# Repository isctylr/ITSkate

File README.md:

# ITSkate
The collection of hardware and software for my electric skateboard project.

The only portion currently available is the remote, which can be found in the "Remote" folder.
  - This includes the hardware for the remote (TX), joystick, and receiver (RX), plus software. More information available in the folder.

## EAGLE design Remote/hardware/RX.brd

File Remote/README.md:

# ITSkate Remote

An open source remote for the VESC based on the arduino samd architecture and the HM-10 BLE module.

To build the board from scratch will require the following items:
	- All 3 finished boards (A BOM is in the works, but can be determined from the EAGLE files under "Hardware").
	- The Arduino IDE with the Arduino SAMD boards installed.
	- The bootloader, which can be loaded by adding http://isaactaylor.net/package_itaylor_index.json to Preferences>Additional Boards Manager URLs, and installing ITSkate Remote from the Board Manager.
	- A j-link, stlink v2, or other programmer for the samd chip. (This guide will use the stlink v2).

## Building the board

## Programming the HM-10s

Programming the HM-10 module takes 6 steps, using the AT commands. You may choose to perform this step later, as the TX software includes an AT passthrough mode.

You can learn more about the HM-10 and it's AT commands from the manual: http://fab.cba.mit.edu/classes/863.15/doc/tutorials/programming/bluetooth/bluetooth40_en.pdf

1. AT
You should recieve OK in return. If nothing appears, make sure you have a genuine HM10 and not a clone, then make sure you are not sending LF or CR, and that your baud rate is 9600 (we will be changing this later, but this is the default).

2. AT+ADDR?
Take note of the address of both the RX and TX.

3. AT+ROLE?
Setting the role will depend on if this is the TX or RX. The TX will be set to AT+ROLE1, because it is the master device. The RX will be set to AT+ROLE0 (left as default).

4. AT+CONxxxxxxxx
Replace the xxxxx with the address of the opposite board, performing the command first on the RX board, then the TX. If both are powered on, you should recieve OK+CONN from the TX.

5. AT+POWE3
Boost the power on both to 6dbm.

6. AT+BAUD4
Set the baud rate of the UART connection to 115200. 

7. AT+RESET
After resetting you'll have to reconnect with the baud rate of 115200. You can type AT to check your work.

## Building the bootloader

## Flashing the bootloader

## Loading the software

Download VescUartControl library by RollingGecko Make sure to choose the
VESC6 branch if you program your vesc with vesc-tool and not bldc.
Add the following lines to VescUart.h:

#ifdef ARDUINO_ARCH_SAMD
#define SERIALIO Serial1  
#define DEBUGSERIAL Serial
#endif

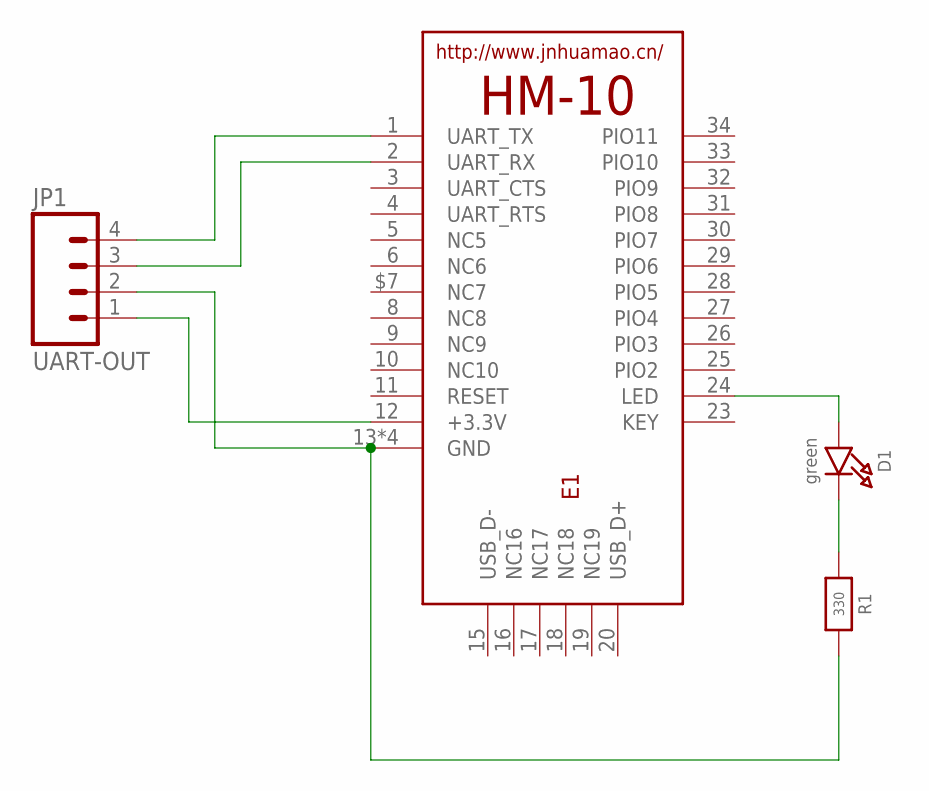
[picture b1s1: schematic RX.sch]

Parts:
D1: green; CHIPLED_0805_NOOUTLINE
E1: HM-10-BOARD; 26.9X13X2.2_BOARD
JP1: UART-OUT; 1X04
R1: 330; 0805-NO

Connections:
unnamed: E1.1 (UART_TX), JP1.4
unnamed: E1.2 (UART_RX), JP1.3
unnamed: E1.13 (GND), E1.14 (GND), E1.21 (GND), E1.22 (GND), JP1.2, R1.2
unnamed: E1.12 (+3.3V), JP1.1
unnamed: D1.A, E1.24 (LED)
unnamed: D1.C, R1.1

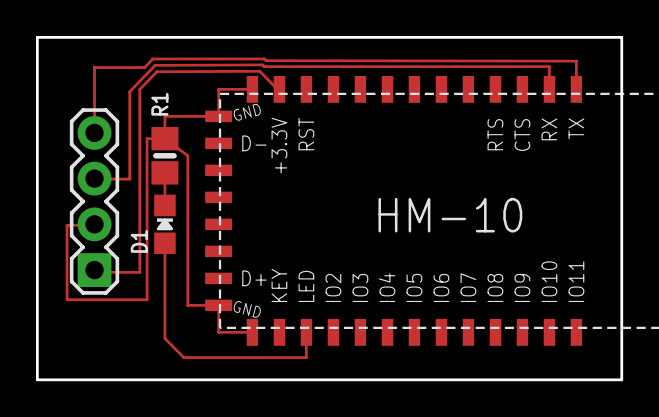
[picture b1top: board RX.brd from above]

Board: 2 copper layers, 32.5 x 19.0 mm, 4 parts (0 on the bottom side), 6 nets.

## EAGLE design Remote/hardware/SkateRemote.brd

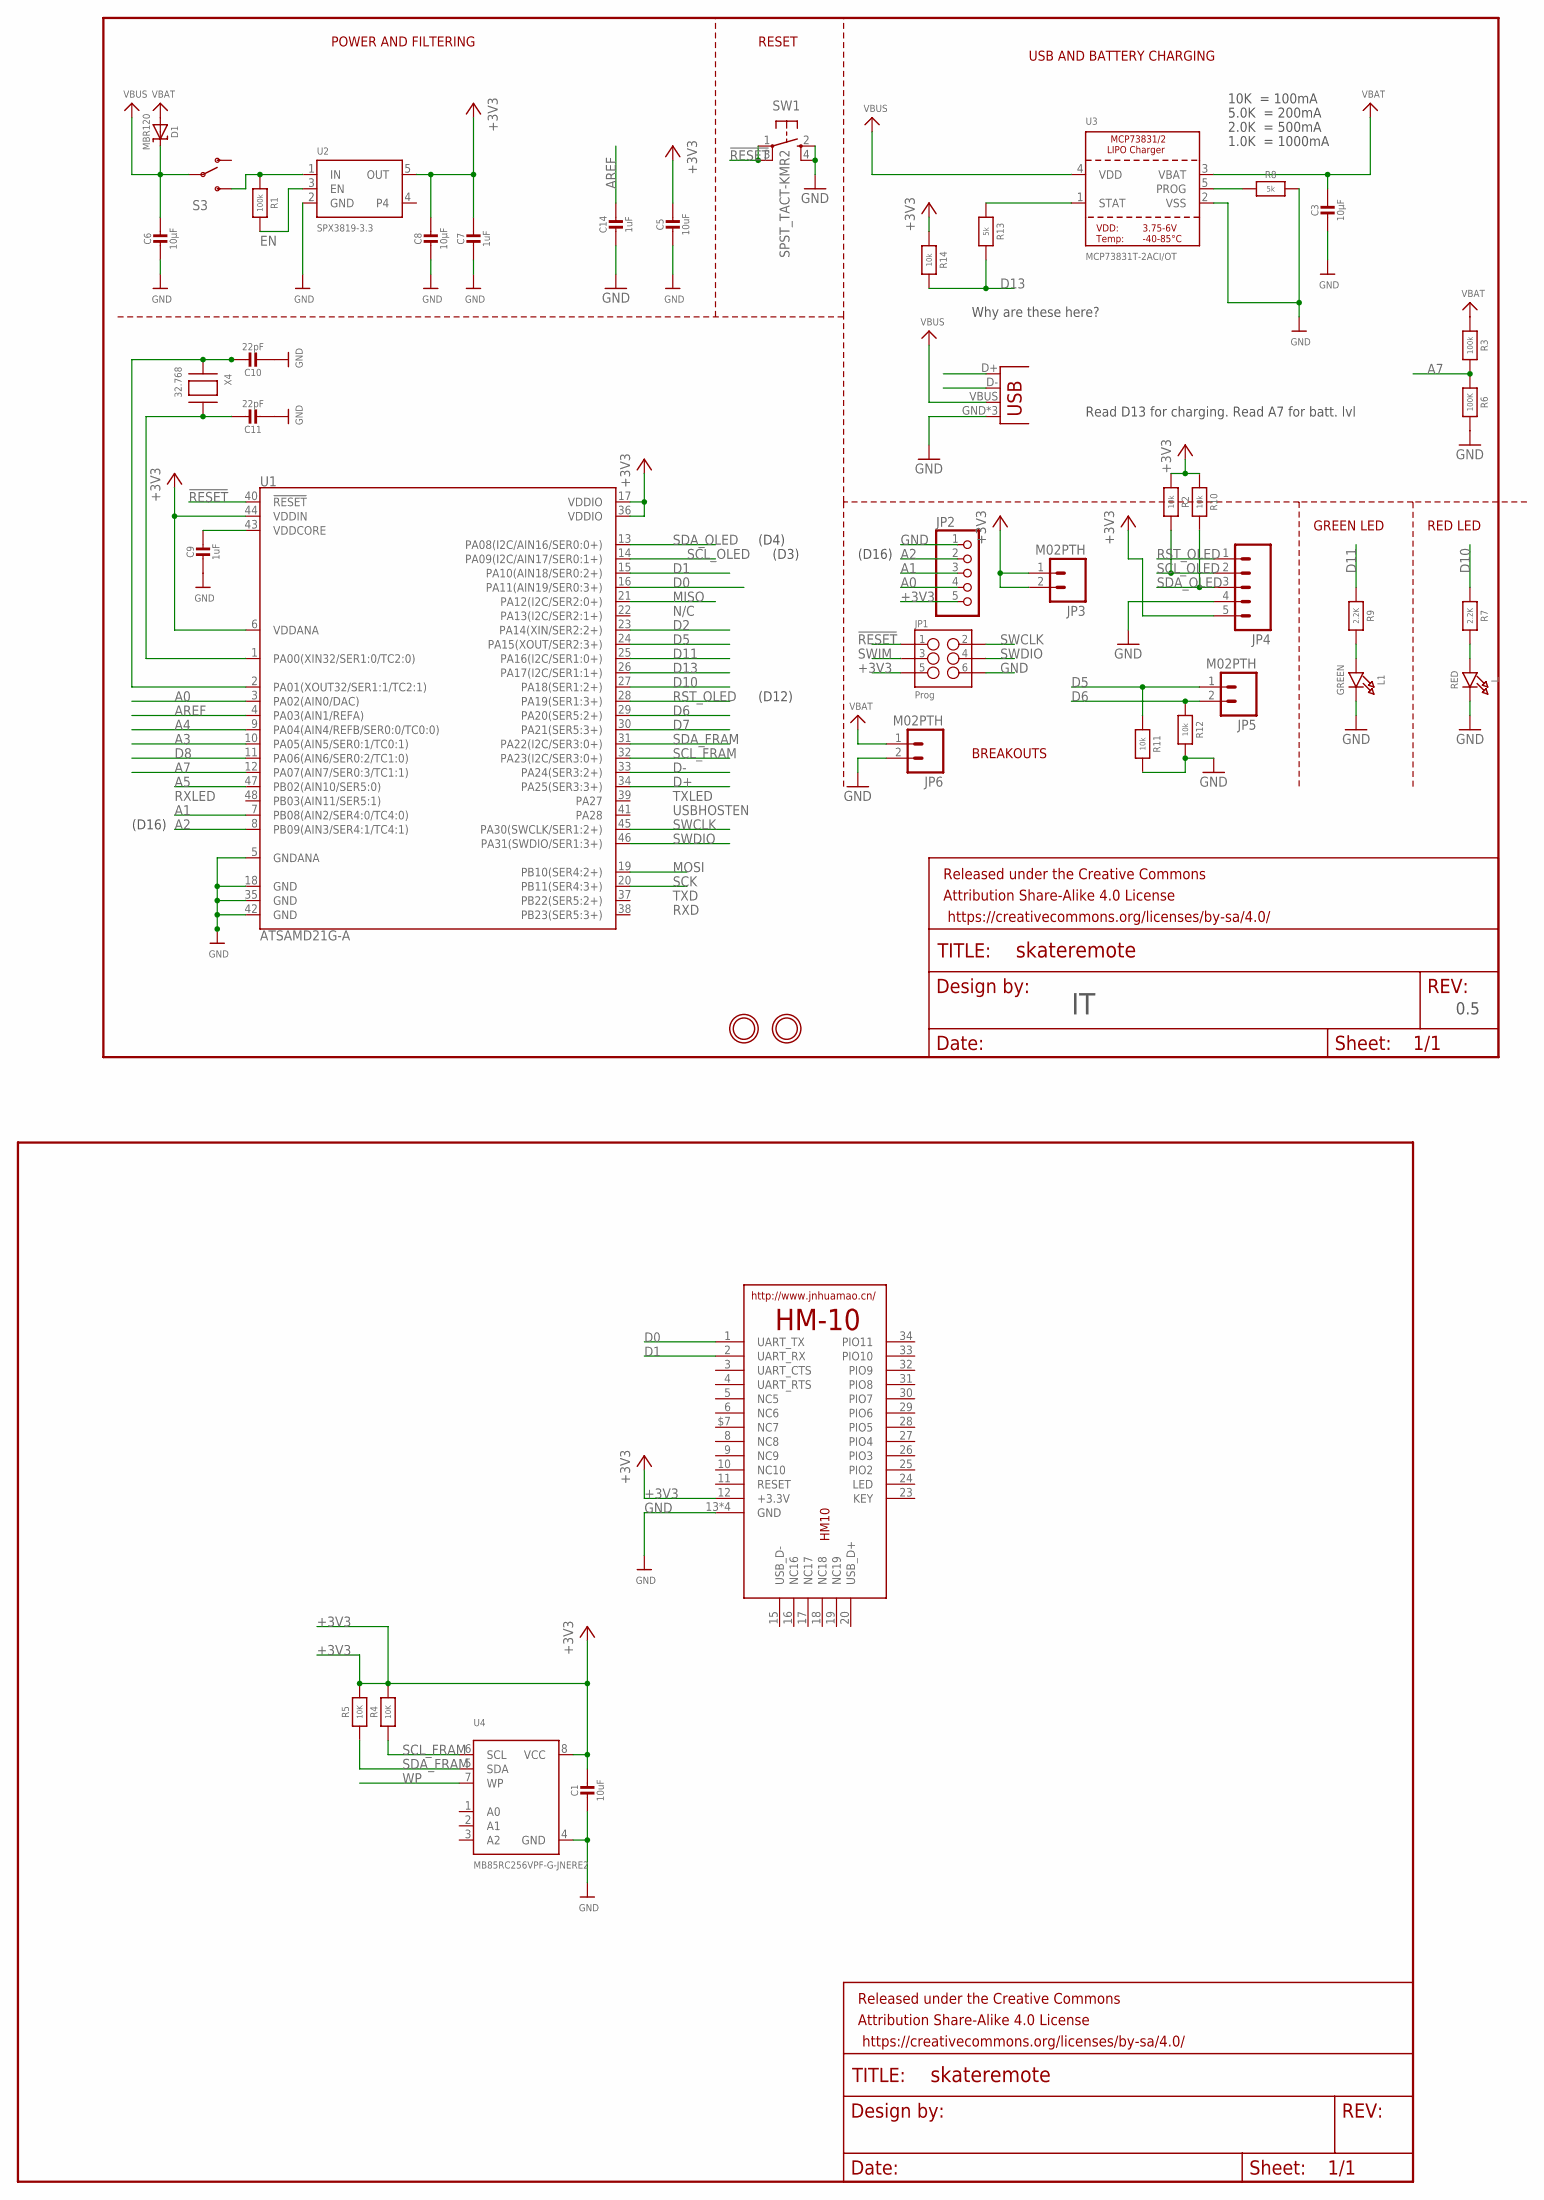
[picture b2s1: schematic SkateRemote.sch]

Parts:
C1: 10uF; _0805MP
C3, C6, C8: 10µF; 0805-NO
C5: 10uF; 0805-NO
C7, C9, C14: 1uF; 0805-NO
C10, C11: 22pF; 0805-NO
D1: MBR120; SOD-123
FRAME2, FRAME3: FRAME-LETTER; CREATIVE_COMMONS
HM10: HM-10-BOARD; 26.9X13X2.2_BOARD
JP1: Prog; 2X3
JP2: PINHD-1X5; 1X05
JP3, JP5, JP6: M02PTH; 1X02
JP4: M05PTH; 1X05
L: RED; CHIPLED_0805_NOOUTLINE
L1: GREEN; CHIPLED_0805_NOOUTLINE
R1, R3: 100k; 0805-NO
R2, R10, R11, R12, R14: 10k; 0805-NO
R4, R5: 10K; _0805MP
R6: 100K; 0805-NO
R7, R9: 2.2K; 0805-NO
R8, R13: 5k; 0805-NO
S3: SWITCH-SPDT-SMD-A; SWITCH-SPST-SMD-A
SW1: SPST_TACT-KMR2; KMR2
U1: ATSAMD21G-A; TQFP-48
U2: SPX3819-3.3; SOT23-5
U3: MCP73831T-2ACI/OT; SOT23-5
U4: MB85RC256VPF-G-JNERE2; SOIC8_208MIL
U$31, U$32: MOUNTINGHOLE2.5; MOUNTINGHOLE_2.5_PLATED
X3: microUSB; USB-MICROB
X4: 32.768; XTAL3215

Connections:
!RESET: JP1.1, SW1.1, SW1.3 (P1), U1.40 (!RESET!)
+3V3: C1.1, C5.1, C7.1, C8.1, HM10.12 (+3.3V), JP1.5, JP2.5, JP3.1, JP3.2, JP4.5, R2.1, R4.2, R5.2, R10.1, R14.1, U1.6 (VDDANA), U1.17 (VDDIO), U1.36 (VDDIO), U1.44 (VDDIN), U2.5 (OUT), U4.8 (VCC)
A0: JP2.4, U1.3 (PA02(AIN0/DAC))
A1: JP2.3, U1.7 (PB08(AIN2/SER4:0/TC4:0))
A2: JP2.2, U1.8 (PB09(AIN3/SER4:1/TC4:1))
A3: U1.10 (PA05(AIN5/SER0:1/TC0:1))
A4: U1.9 (PA04(AIN4/REFB/SER0:0/TC0:0))
A5: U1.47 (PB02(AIN10/SER5:0))
A7: R3.2, R6.1, U1.12 (PA07(AIN7/SER0:3/TC1:1))
AREF: C14.1, U1.4 (PA03(AIN1/REFA))
D0: HM10.1 (UART_TX), U1.16 (PA11(AIN19/SER0:3+))
D1: HM10.2 (UART_RX), U1.15 (PA10(AIN18/SER0:2+))
D2: U1.23 (PA14(XIN/SER2:2+))
D5: JP5.1, R11.1, U1.24 (PA15(XOUT/SER2:3+))
D6: JP5.2, R12.1, U1.29 (PA20(SER5:2+))
D7: U1.30 (PA21(SER5:3+))
D8: U1.11 (PA06(AIN6/SER0:2/TC1:0))
D10: R7.1, U1.27 (PA18(SER1:2+))
D11: R9.1, U1.25 (PA16(I2C/SER1:0+))
D13: R13.2, R14.2, U1.26 (PA17(I2C/SER1:1+))
D+: U1.34 (PA25(SER3:3+)), X3.D+
D-: U1.33 (PA24(SER3:2+)), X3.D-
EN: R1.2, U2.3 (EN)
GND: C1.2, C3.2, C5.2, C6.2, C7.2, C8.2, C9.2, C10.2, C11.2, C14.2, HM10.13 (GND), HM10.14 (GND), HM10.21 (GND), HM10.22 (GND), JP1.6, JP2.1, JP4.4, JP6.2, L.C, L1.C, R6.2, R8.2, R11.2, R12.2, SW1.2 (S), SW1.4 (S1), U1.5 (GNDANA), U1.18 (GND), U1.35 (GND), U1.42 (GND), U2.2 (GND), U3.2 (VSS), U4.4 (GND), X3.GND, X3.MT1 (GND), X3.MT2 (GND)
MISO: U1.21 (PA12(I2C/SER2:0+))
MOSI: U1.19 (PB10(SER4:2+))
unnamed: R13.1, U3.1 (STAT)
unnamed: L.A, R7.2
unnamed: R8.1, U3.5 (PROG)
unnamed: R1.1, S3.3 (S), U2.1 (IN)
unnamed: L1.A, R9.2
unnamed: C10.1, U1.2 (PA01(XOUT32/SER1:1/TC2:1)), X4.P$1
unnamed: C11.1, U1.1 (PA00(XIN32/SER1:0/TC2:0)), X4.P$2
RST_OLED: JP4.1, U1.28 (PA19(SER1:3+))
SCK: U1.20 (PB11(SER4:3+))
SCL_FRAM: R4.1, U1.32 (PA23(I2C/SER3:0+)), U4.6 (SCL)
SCL_OLED: JP4.2, R2.2, U1.14 (PA09(I2C/AIN17/SER0:1+))
SDA_FRAM: R5.1, U1.31 (PA22(I2C/SER3:0+)), U4.5 (SDA)
SDA_OLED: JP4.3, R10.2, U1.13 (PA08(I2C/AIN16/SER0:0+))
SWCLK: JP1.2, U1.45 (PA30(SWCLK/SER1:2+))
SWDIO: JP1.4, U1.46 (PA31(SWDIO/SER1:3+))
SWIM: JP1.3
VBAT: C3.1, D1.A, JP6.1, R3.1, U3.3 (VBAT)
VBUS: C6.1, D1.C, S3.2, U3.4 (VDD), X3.VBUS
VDDCORE: C9.1, U1.43 (VDDCORE)
WP: U4.7 (WP)

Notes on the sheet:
POWER AND FILTERING
RESET
10K = 100mA
5.0K = 200mA
2.0K = 500mA
1.0K = 1000mA
USB AND BATTERY CHARGING
BREAKOUTS
RED LED
RXLED
N/C
TXLED
USBHOSTEN
TXD
RXD
(D4)
(D3)
(D12)
(D16)
GREEN LED
Read D13 for charging. Read A7 for batt. lvl
Why are these here?
0.5

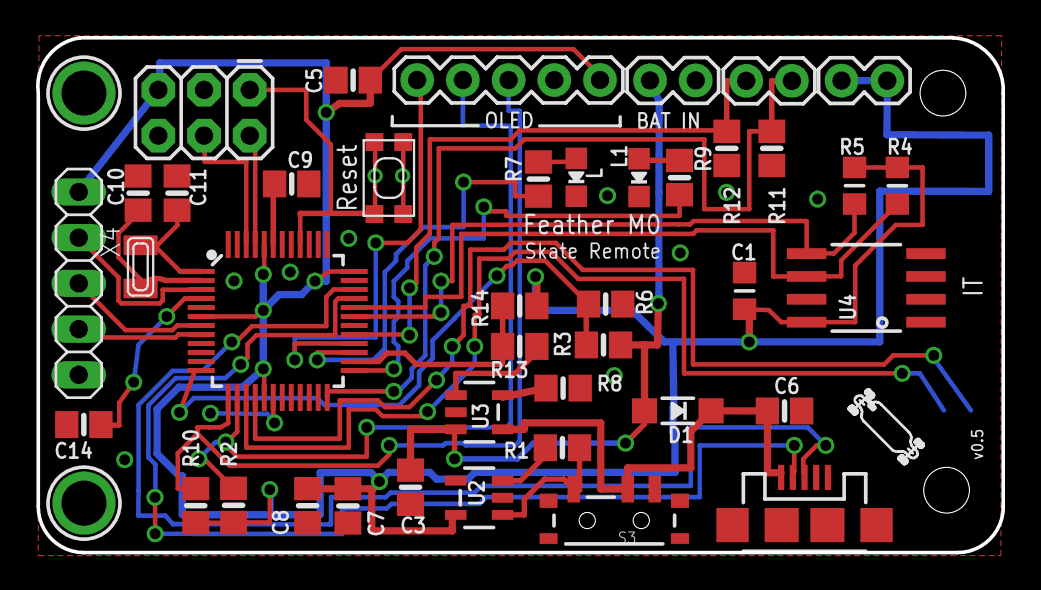
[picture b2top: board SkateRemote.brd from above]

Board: 2 copper layers, 53.6 x 28.6 mm, 46 parts (1 on the bottom side), 35 nets.

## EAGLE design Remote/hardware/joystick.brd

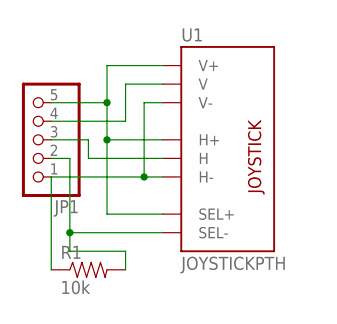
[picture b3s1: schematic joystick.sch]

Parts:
JP1: PINHD-1X5; 1X05
R1: 10k; 0805
U1: JOYSTICKPTH; JOYSTICK

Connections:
BTN: JP1.2, R1.2, U1.B2A (SEL-)
GND: JP1.1, R1.1, U1.H3 (H-), U1.V3 (V-)
VCC: JP1.5, U1.B1A (SEL+), U1.H1 (H+), U1.V1 (V+)
X: JP1.4, U1.V2 (V)
Y: JP1.3, U1.H2 (H)

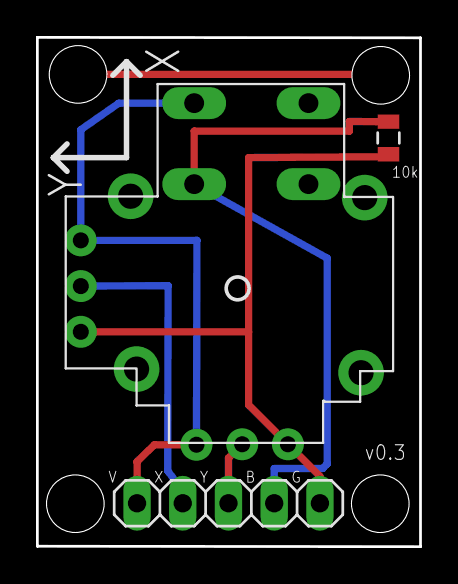
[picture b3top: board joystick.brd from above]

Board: 2 copper layers, 21.3 x 28.3 mm, 3 parts (0 on the bottom side), 5 nets.

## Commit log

2017-06-26 First Upload
2017-10-14 Added some to the readme before I forget. Added a zip with the working UART Library for VESC6.

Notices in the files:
parts and their libraries:
SparkFun-Connectors: Licensing: Creative Commons ShareAlike 4.0 International - https://creativecommons.org/licenses/by-sa/4.0
microbuilder: This work is placed in the public domain, and may be freely used for commercial and non-commercial work with the following conditions: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
